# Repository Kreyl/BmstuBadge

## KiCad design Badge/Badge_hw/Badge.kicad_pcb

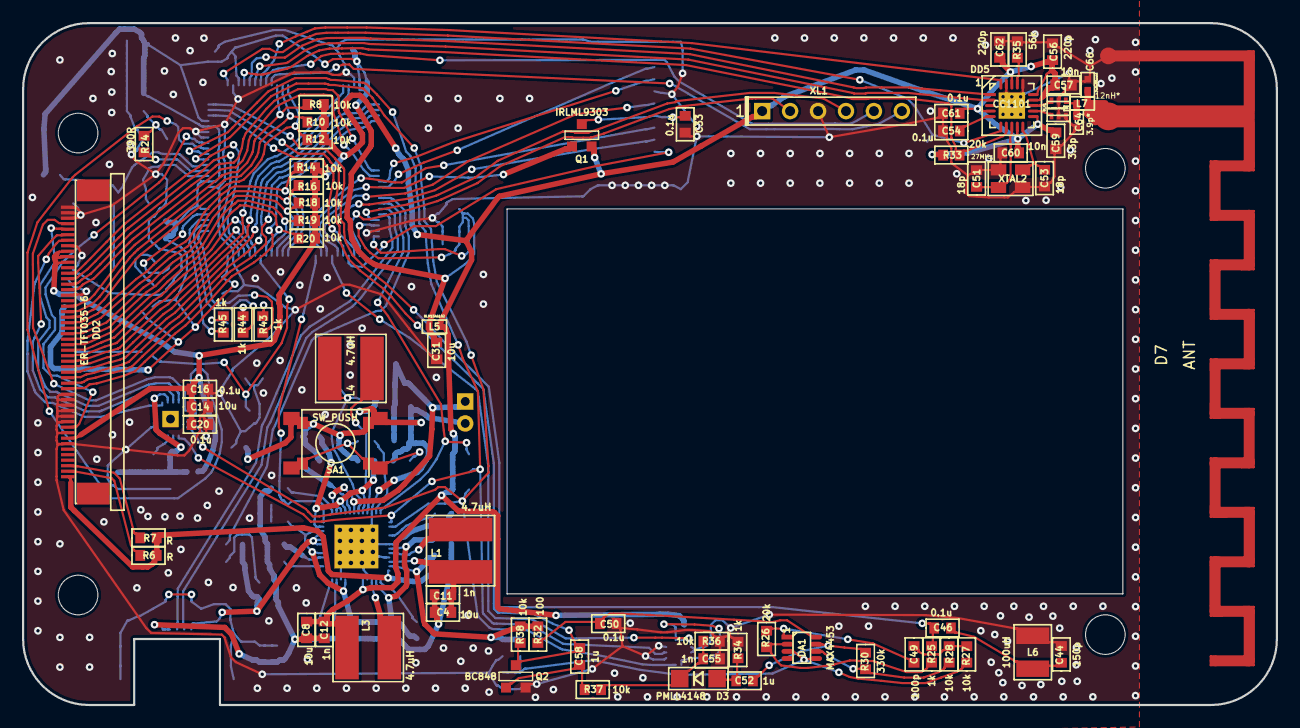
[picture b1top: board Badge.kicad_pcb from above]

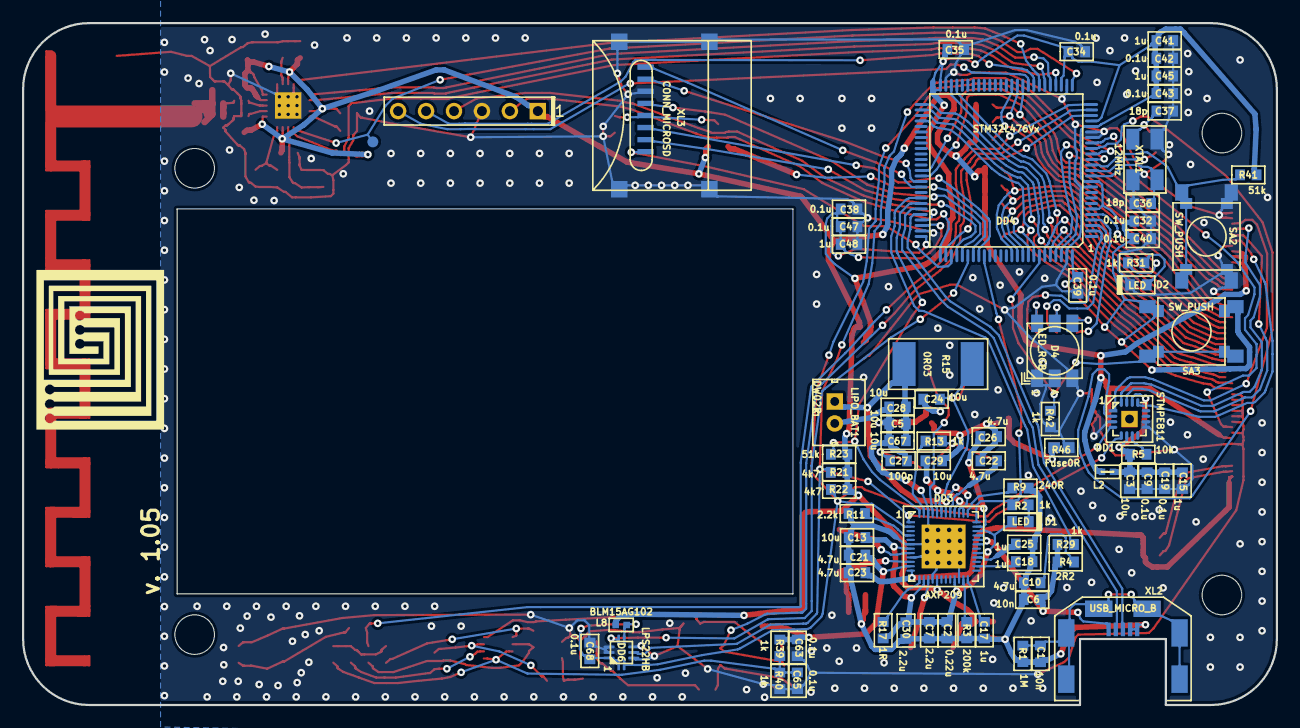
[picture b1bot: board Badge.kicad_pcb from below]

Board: 2 copper layers, 114.0 x 62.0 mm, 147 parts (77 on the bottom side), 118 nets.

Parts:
BLN1: BALUN868JOHANSON; BALUN_JOHANSON868
C1, C6, C57, C60: 10n; CAP_0603
C2: 0.22u; CAP_0603
C3, C4, C5, C8, C13, C14, C24, C28, C29, C31, C67: 10u; CAP_0603
C7, C30: 2.2u; CAP_0603
C9, C16, C19, C20, C32, C33, C34, C35, C38, C39, C40, C41, C43, C46, C47, C50, C54, C61, C63, C65, C68: 0.1u; CAP_0603
C10, C21, C22, C23, C26: 4.7u; CAP_0603
C11, C12, C55: 1n; CAP_0603
C15, C17, C18, C25, C42, C45, C48, C52, C58: 1u; CAP_0603
C27, C49: 100p; CAP_0603
C36, C37, C51, C53: 18p; CAP_0603
C44: 150p; CAP_0603
C56, C62: 220p; CAP_0603
C59: 3.3p; CAP_0603
C64: 3.9p*; CAP_0402
C66: DoNotMount; CAP_0402
D1, D2: LED; LED_0603
D3: PMLL4148; SOD80C
D4: LED_RGB; LED_5050
D7: ANT; ANTENNA_868_INV_F_SHARP
DA1: MAX4453; SOT23-8
DD1: STMPE811; QFN16_4x4_H
DD2: ER-TFT035-6; ER-CON50HT-1
DD3: AXP209; QFN48_EP_6x6_Pitch0.4mm
DD4: STM32L476Vx; LQFP100
DD5: CC1101; QFN20
DD6: LPS22HB; 10_2X2
L1, L3, L4: 4.7uH; IND_SDR0604
L2, L5, L8: BLM15AG102; IND_0402
L6: 100uH; IND_1812
L7: 12nH*; IND_0402
LIPO_BAT1: DW02R; WB-02(MW-2M)
Q1: IRLML9303; SOT23-3
Q2: BC848; SOT23-3
R1: 1M; RES_0603
R2, R13, R25, R29, R31, R34, R39, R40, R42, R43, R44, R45: 1k; RES_0603
R3: 200k; RES_0603
R4: 2R2; RES_0603
R5, R8, R10, R12, R14, R16, R18, R19, R20, R27, R28, R36, R37, R38: 10k; RES_0603
R6, R7: R; RES_0603
R9: 240R; RES_0603
R11: 2.2k; RES_0603
R15: 0R03; RES_2512
R17: 1R; RES_0603
R21, R22: 4k7; RES_0603
R23, R41: 51k; RES_0603
R24: 390R; RES_0603
R26, R33: 20k; RES_0603
R30: 330k; RES_0603
R32: 100; RES_0603
R35: 56k; RES_0603
R46: Fuse0R; RES_0603_FUSE
SA1, SA2, SA3: SW_PUSH; BTN_6x6_4x4
TP1: TESTPOINT; TESTPOINT_1MM
XL1: CONN_6; PLS-6
XL2: USB_MICRO_B; USBmicro_MOLEX_WM17142
XL3: CONN_MICROSD; MICROSD_CAP_FIX05A
XTAL1: 12MHz; 0503x4-4
XTAL2: 27MHz; 03225C4

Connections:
+2V5: C21.1, C63.1, DD3.11, R32.2, R38.2, R39.1
+3V3: C8.1, C12.1, C14.1, C16.1, C20.1, C56.1, C57.1, C59.1, C60.1, C61.1, C62.1, DD2.8, DD2.40, DD2.41, DD2.42, DD3.17, DD5.4, DD5.9, DD5.11, DD5.14, DD5.15, DD5.18, L2.2, L3.1, L5.2, L8.2, Q1.2, R8.2, R10.2, R12.2, R14.2, R16.2, R18.2, R19.2, R20.2, R21.2, R22.2, R23.2, R33.2, XL1.1
+3V3_120mA: C23.1, DD2.1, DD3.12, R6.2, R7.2
+5V: C6.1, DD3.31, DD3.32, DD3.33, R4.1, R29.1, XL2.1
+BATT: C5.1, C28.1, C67.1, DD3.38, DD3.39, DD3.42, LIPO_BAT1.1, R15.1
/ANT1: BLN1.1, C64.1, L7.2
/ANT2: C66.1, D7.~, L7.1
/CC_CS: DD4.29, DD5.7, R33.1
/CC_GDO0: DD4.26, DD5.6, TP1.1
/CC_MISO: DD4.31, DD5.2
/CC_MOSI: DD4.32, DD5.20
/CC_SCK: DD4.30, DD5.1
/CHARGING: DD3.36, DD4.84, R2.1
/DB0: DD2.32, DD4.35, R8.1
/DB1: DD2.31, DD4.36, R10.1
/DB2: DD2.30, DD4.37, R12.1
/DB3: DD2.29, DD4.89, R14.1
/DB4: DD2.28, DD4.90, R16.1
/DB5: DD2.27, DD4.91, R18.1
/DB6: DD2.26, DD4.92, R19.1
/DB7: DD2.25, DD4.93, R20.1
/DB8: DD2.24, DD4.95
/DB9: DD2.23, DD4.96
/DB10: DD2.22, DD4.47
/DB11: DD2.21, DD4.48
/DB12: DD2.20, DD4.51
/DB13: DD2.19, DD4.52
/DB14: DD2.18, DD4.53
/DB15: DD2.17, DD4.54
/DCDC_2: C4.1, C11.1, DD3.10, L1.1
/LCD_CS: DD2.38, DD4.97
/LCD_D/I_SLC: DD2.37, DD4.98
/LCD_RD: DD2.35, DD4.64
/LCD_RESET: DD2.10, DD4.18
/LCD_WR: DD2.36, DD4.63
/LCD_X+: DD1.13, DD2.44
/LCD_X-: DD1.16, DD2.46
/LCD_Y+: DD1.15, DD2.45
/LCD_Y-: DD1.1, DD2.47
/LDO_1: C25.1, DD3.28
/LDO_3: C22.1, DD3.41
/LX_2: DD3.8, L1.2
/LX_3: DD3.15, L3.2
/PRESSURE_INT: DD4.81, DD6.7
/PWR_IRQ: DD3.48, DD4.69, R23.1
/PWR_UNST: C2.1, C7.1, C13.1, C26.1, C29.2, C30.1, D1.A, DD3.7, DD3.14, DD3.21, DD3.29, DD3.34, DD3.35, DD3.40, DD3.44, R17.1
/RF1: BLN1.4, DD5.12
/RF2: BLN1.3, DD5.13
/SCL: DD1.4, DD3.2, DD4.15, DD6.2, R22.1
/SDA: DD1.5, DD3.1, DD4.16, DD6.4, R21.1
/SD_CLK: DD4.80, XL3.5
/SD_CMD: DD4.83, XL3.3
/SD_DAT0: DD4.65, XL3.7
/SD_DAT1: DD4.66, XL3.8
/SD_DAT2: DD4.78, XL3.1
/SD_DAT3: DD4.79, XL3.2
/SD_POWER: DD4.82, Q1.1
/SWD_CLK: DD4.76, XL1.2
/SWD_IO: DD4.72, XL1.4
/TOUCH_INT: DD1.2, DD4.17
/TOUCH_PWR: C3.1, C9.1, C15.1, C19.1, DD1.6, DD1.14, L2.1, R5.2
/UART_RX: DD4.34, XL1.6
/UART_TX: DD4.33, XL1.5
/USB_D+: DD4.71, XL2.3
/USB_D-: DD4.70, XL2.2
/klNFC_Modulation: DD4.23, DD4.77
/klNFC_Rx: C58.1, DD4.24, Q2.3, R38.1
/klNFC_Tx: C46.1, DD4.25, R25.2
GNDA: C1.2, C2.2, C4.2, C5.2, C6.2, C7.2, C8.2, C10.1, C11.2, C12.2, C13.2, C17.2, C18.2, C21.2, C22.2, C23.2, C24.2, C25.2, C26.2, C27.2, C28.2, C29.1, C30.2, C67.2, DD3.6, DD3.9, DD3.16, DD3.22, DD3.46, DD3.PAD, LIPO_BAT1.2, R1.2, R3.2, R9.1, R11.1, R46.1, SA1.2, XL2.4, XL2.5
GNDS: BLN1.2, BLN1.5, BLN1.6, C3.2, C9.2, C14.2, C15.2, C16.2, C19.2, C20.2, C31.2, C32.2, C33.2, C34.2, C35.2, C36.2, C37.2, C38.2, C39.2, C40.2, C41.2, C42.2, C43.2, C44.2, C45.2, C47.2, C48.2, C50.1, C51.2, C53.2, C54.2, C55.2, C56.2, C57.2, C59.2, C60.2, C61.2, C62.2, C63.2, C64.2, C65.2, C66.2, C68.2, D2.C, D4.1, D4.2, D4.3, D7.GND, DD1.3, DD1.9, DD1.10, DD2.7, DD2.9, DD2.11, DD2.12, DD2.13, DD2.14, DD2.15, DD2.16, DD2.34, DD2.43, DD2.48, DD2.49, DD2.50, DD4.10, DD4.19, DD4.20, DD4.27, DD4.49, DD4.74, DD4.99, DD5.16, DD5.19, DD5.PAD, DD6.3, DD6.5, DD6.8, DD6.9, L6.2, Q2.2, R34.1, R35.2, R36.1, R40.2, R42.1, R46.2, SA2.1, XL1.3, XL3.6, XL3.H, XTAL1.H, XTAL2.H
MCU_PWR: C31.1, C32.1, C34.1, C35.1, C38.1, C39.1, C40.1, C41.1, C42.1, C43.1, C45.1, C47.1, C48.1, DD4.6, DD4.11, DD4.21, DD4.22, DD4.28, DD4.50, DD4.73, DD4.75, DD4.100, L5.1, R41.2, SA3.2
unnamed: C1.1, R1.1, XL2.SHLD
unnamed: C10.2, R4.2
unnamed: C17.1, DD3.24
unnamed: C18.1, DD3.26
unnamed: C24.1, DD3.43, L4.1, R15.2
unnamed: C27.1, R13.1, SA1.1
unnamed: C33.1, Q1.3, XL3.4
unnamed: C36.1, DD4.12, XTAL1.1
unnamed: C37.1, R24.2, XTAL1.2
unnamed: C44.1, C46.2, L6.1
unnamed: C49.1, R27.2, R28.1
unnamed: C49.2, DA1.1, R26.1
unnamed: C50.2, DA1.8, R32.1
unnamed: C51.1, DD5.8, XTAL2.1
unnamed: C52.1, D3.A, R34.2
unnamed: C52.2, DA1.7, R30.1
unnamed: C53.1, DD5.10, XTAL2.2
unnamed: C54.1, DD5.5
unnamed: C55.1, D3.C, R36.2, R37.1
unnamed: C58.2, Q2.1, R37.2
unnamed: C68.1, DD6.1, DD6.6, DD6.10, L8.1
unnamed: D1.C, R2.2
unnamed: D2.A, R31.2
unnamed: D4.4, R45.1
unnamed: D4.5, R44.1
unnamed: D4.6, R43.1
unnamed: DA1.2, R25.1, R26.2
unnamed: DA1.6, R28.2, R30.2
unnamed: DD1.7, R5.1
unnamed: DD2.2, R6.1
unnamed: DD2.3, R7.1
unnamed: DD3.4, R11.2
unnamed: DD3.13, R17.2
unnamed: DD3.23, R3.1
unnamed: DD3.37, R9.2
unnamed: DD3.45, L4.2
unnamed: DD3.47, R13.2
unnamed: DD4.2, R43.2
unnamed: DD4.3, R44.2
unnamed: DD4.4, R45.2
unnamed: DD4.5, R31.1
unnamed: DD4.13, R24.1
unnamed: DD4.14, R41.1, SA2.2
unnamed: DD4.68, R29.2
unnamed: DD4.94, R42.2, SA3.1
unnamed: DD5.17, R35.1
VGND: C65.1, DA1.3, DA1.5, R27.1, R39.2, R40.1

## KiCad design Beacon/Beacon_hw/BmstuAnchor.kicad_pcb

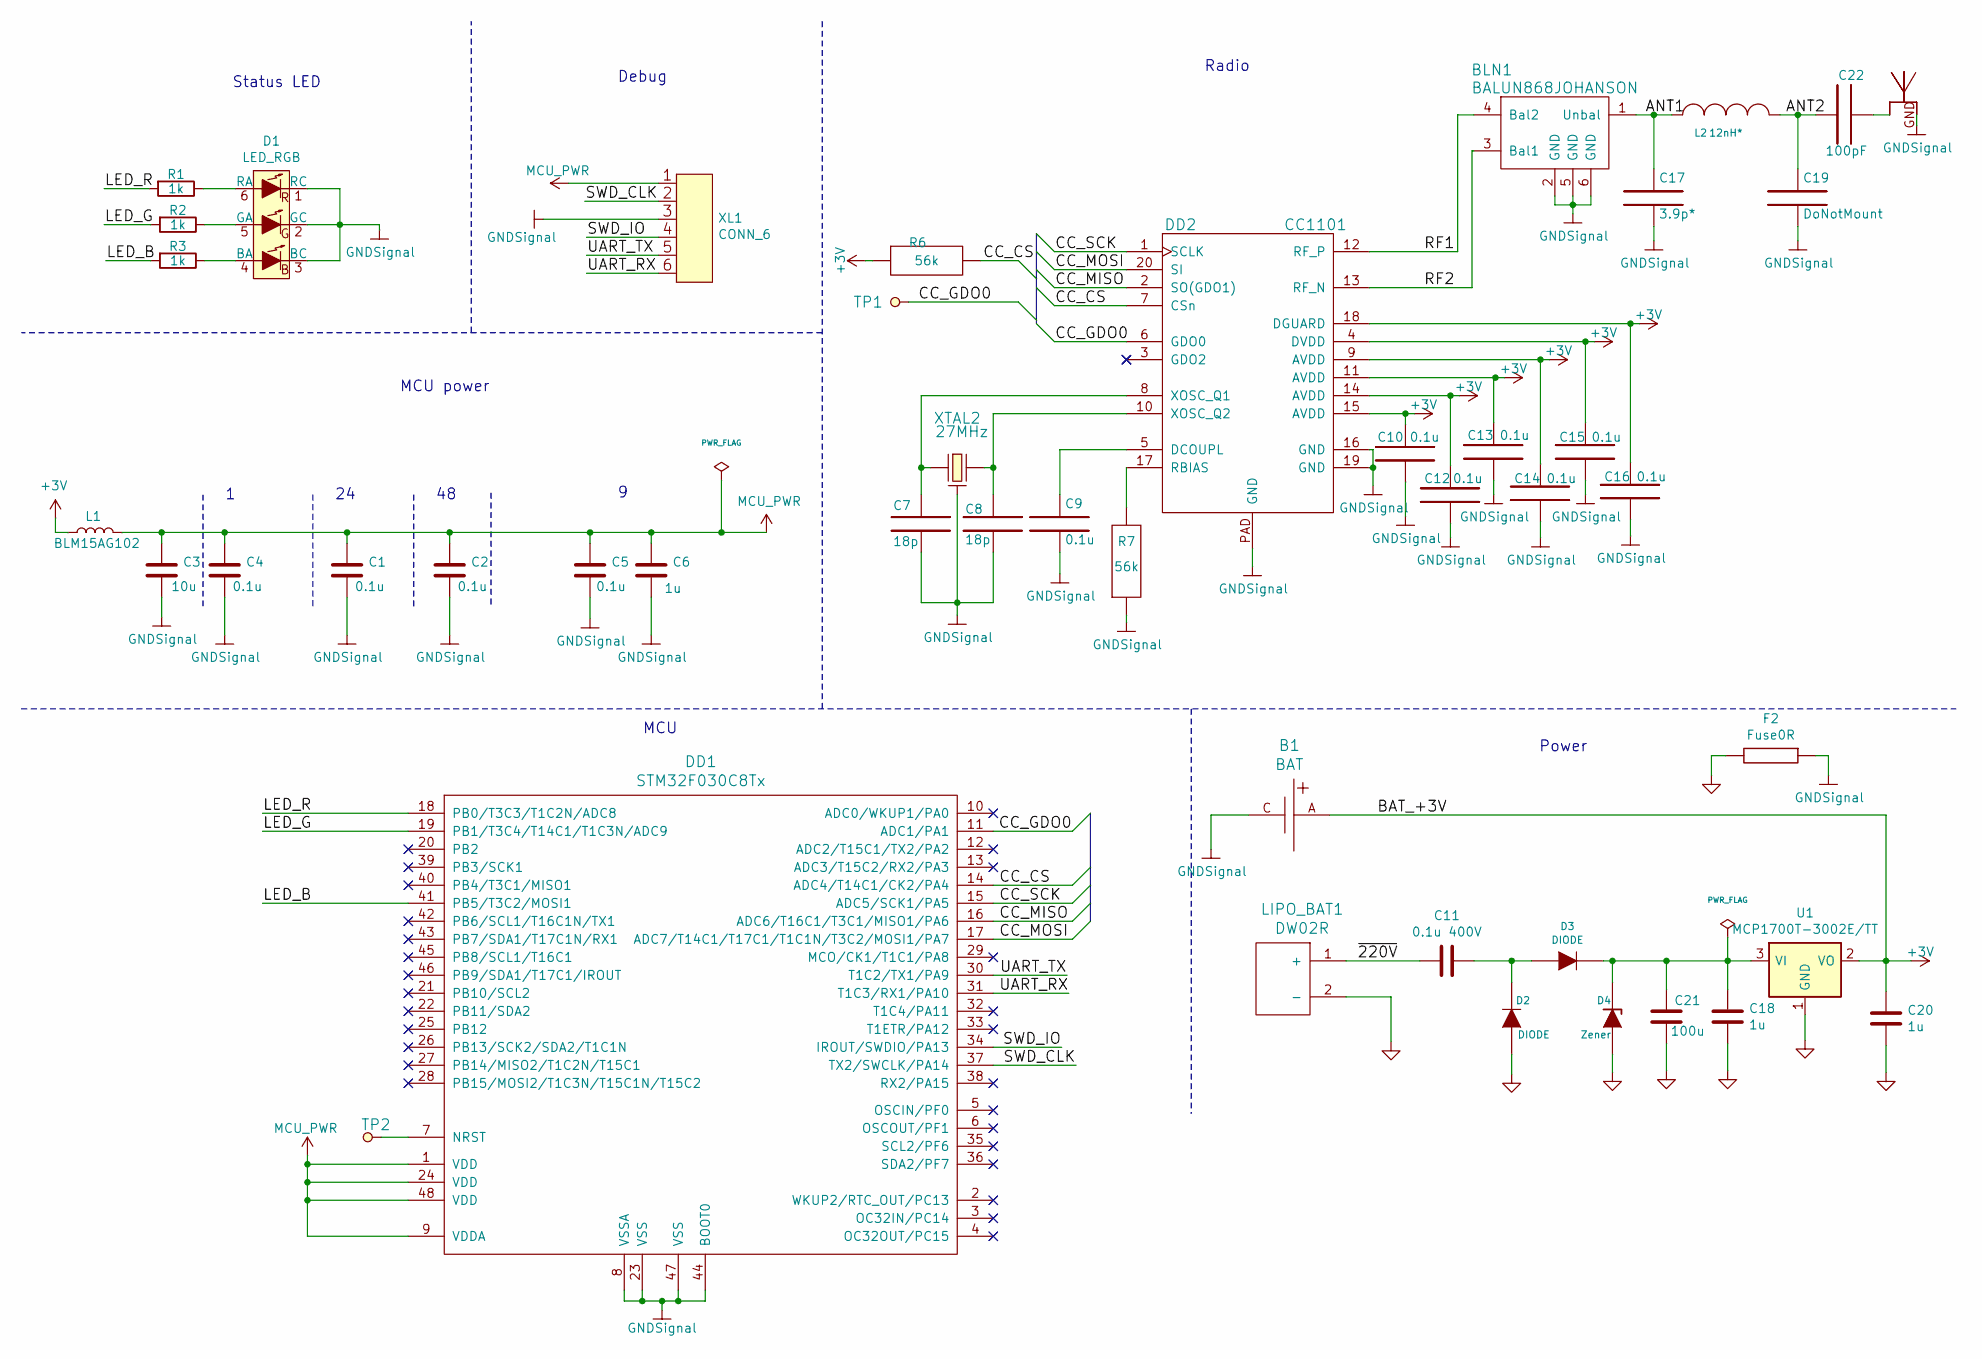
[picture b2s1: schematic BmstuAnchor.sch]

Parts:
B1: BAT; BATTERY_CH7410
BLN1: BALUN868JOHANSON; BALUN_JOHANSON868
C1, C2, C4, C5, C9, C10, C12, C13, C14, C15, C16: 0.1u; CAP_0603
C3: 10u; CAP_0603
C6, C18, C20: 1u; CAP_0603
C7, C8: 18p; CAP_0603
C11: 0.1u 400V; CAP_1812
C17: 3.9p*; CAP_0402
C19: DoNotMount; CAP_0402
C21: 100u; CAP_1210
C22: 100pF; CAP_0402
D1: LED_RGB; LED_5050
D2, D3: DIODE; SMA_DO214AC
D4: Zener; SOT23-3
D5: ANT; ANTENNA_868_INV_F_SHARP
DD1: STM32F030C8Tx; LQFP48
DD2: CC1101; QFN20
F2: Fuse0R; RES_0603_FUSE
L1: BLM15AG102; IND_0402
L2: 12nH*; IND_0402
LIPO_BAT1: DW02R; PLS-2-wide
R1, R2, R3: 1k; RES_0603
R6, R7: 56k; RES_0603
TP1, TP2: TESTPOINT; TESTPOINT_1MM
U1: MCP1700T-3002E/TT; SOT23-3
XL1: CONN_6; PLS-6
XTAL2: 27MHz; 03225C4

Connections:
+3V: B1.A, C10.1, C12.1, C13.1, C14.1, C15.1, C16.1, C20.1, DD2.4 (DVDD), DD2.9 (AVDD), DD2.11 (AVDD), DD2.14 (AVDD), DD2.15 (AVDD), DD2.18 (DGUARD), L1.1, R6.2, U1.2 (VO)
/ANT1: BLN1.1 (Unbal), C17.1, L2.2
/ANT2: C19.1, C22.2, L2.1
/CC_CS: DD1.14 (ADC4/T14C1/CK2/PA4), DD2.7 (CSn), R6.1
/CC_GDO0: DD1.11 (ADC1/PA1), DD2.6 (GDO0), TP1.1
/CC_MISO: DD1.16 (ADC6/T16C1/T3C1/MISO1/PA6), DD2.2 (SO(GDO1))
/CC_MOSI: DD1.17 (ADC7/T14C1/T17C1/T1C1N/T3C2/MOSI1/PA7), DD2.20 (SI)
/CC_SCK: DD1.15 (ADC5/SCK1/PA5), DD2.1 (SCLK)
/LED_B: DD1.41 (PB5/T3C2/MOSI1), R3.2
/LED_G: DD1.19 (PB1/T3C4/T14C1/T1C3N/ADC9), R2.2
/LED_R: DD1.18 (PB0/T3C3/T1C2N/ADC8), R1.2
/RF1: BLN1.4 (Bal2), DD2.12 (RF_P)
/RF2: BLN1.3 (Bal1), DD2.13 (RF_N)
/SWD_CLK: DD1.37 (TX2/SWCLK/PA14), XL1.2
/SWD_IO: DD1.34 (IROUT/SWDIO/PA13), XL1.4
/UART_RX: DD1.31 (T1C3/RX1/PA10), XL1.6
/UART_TX: DD1.30 (T1C2/TX1/PA9), XL1.5
/~220V: C11.2, LIPO_BAT1.1 (+)
GND: C18.2, C20.2, C21.2, D2.A, D4.1, F2.2, LIPO_BAT1.2 (-), U1.1 (GND)
GNDS: B1.C, BLN1.2 (GND), BLN1.5 (GND), BLN1.6 (GND), C1.2, C2.2, C3.2, C4.2, C5.2, C6.2, C7.2, C8.2, C9.2, C10.2, C12.2, C13.2, C14.2, C15.2, C16.2, C17.2, C19.2, D1.1 (RC), D1.2 (GC), D1.3 (BC), D5.GND, DD1.8 (VSSA), DD1.23 (VSS), DD1.44 (BOOT0), DD1.47 (VSS), DD2.16 (GND), DD2.19 (GND), DD2.PAD (GND), F2.1, R7.2, XL1.3, XTAL2.H
MCU_PWR: C1.1, C2.1, C3.1, C4.1, C5.1, C6.1, DD1.1 (VDD), DD1.9 (VDDA), DD1.24 (VDD), DD1.48 (VDD), L1.2, XL1.1
unnamed: C7.1, DD2.8 (XOSC_Q1), XTAL2.1
unnamed: C8.1, DD2.10 (XOSC_Q2), XTAL2.2
unnamed: C9.1, DD2.5 (DCOUPL)
unnamed: C11.1, D2.C, D3.A
unnamed: C18.1, C21.1, D3.C, D4.3, U1.3 (VI)
unnamed: C22.1, D5.~
unnamed: D1.4 (BA), R3.1
unnamed: D1.5 (GA), R2.1
unnamed: D1.6 (RA), R1.1
unnamed: DD1.7 (NRST), TP2.1
unnamed: DD2.17 (RBIAS), R7.1

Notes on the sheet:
Radio
Debug
Status LED
MCU power
MCU
Power

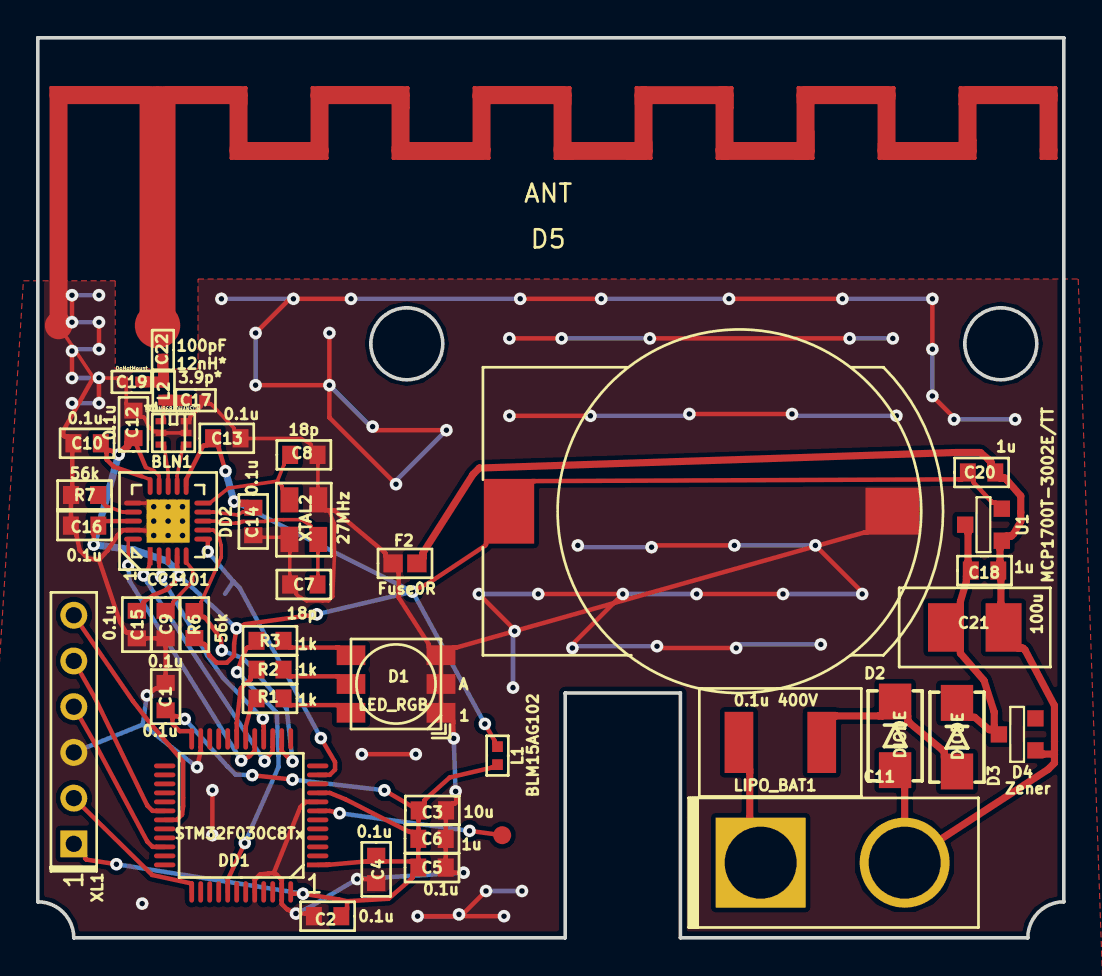
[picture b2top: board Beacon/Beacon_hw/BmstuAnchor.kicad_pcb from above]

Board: 2 copper layers, 57.0 x 50.0 mm, 45 parts (1 on the bottom side), 32 nets.

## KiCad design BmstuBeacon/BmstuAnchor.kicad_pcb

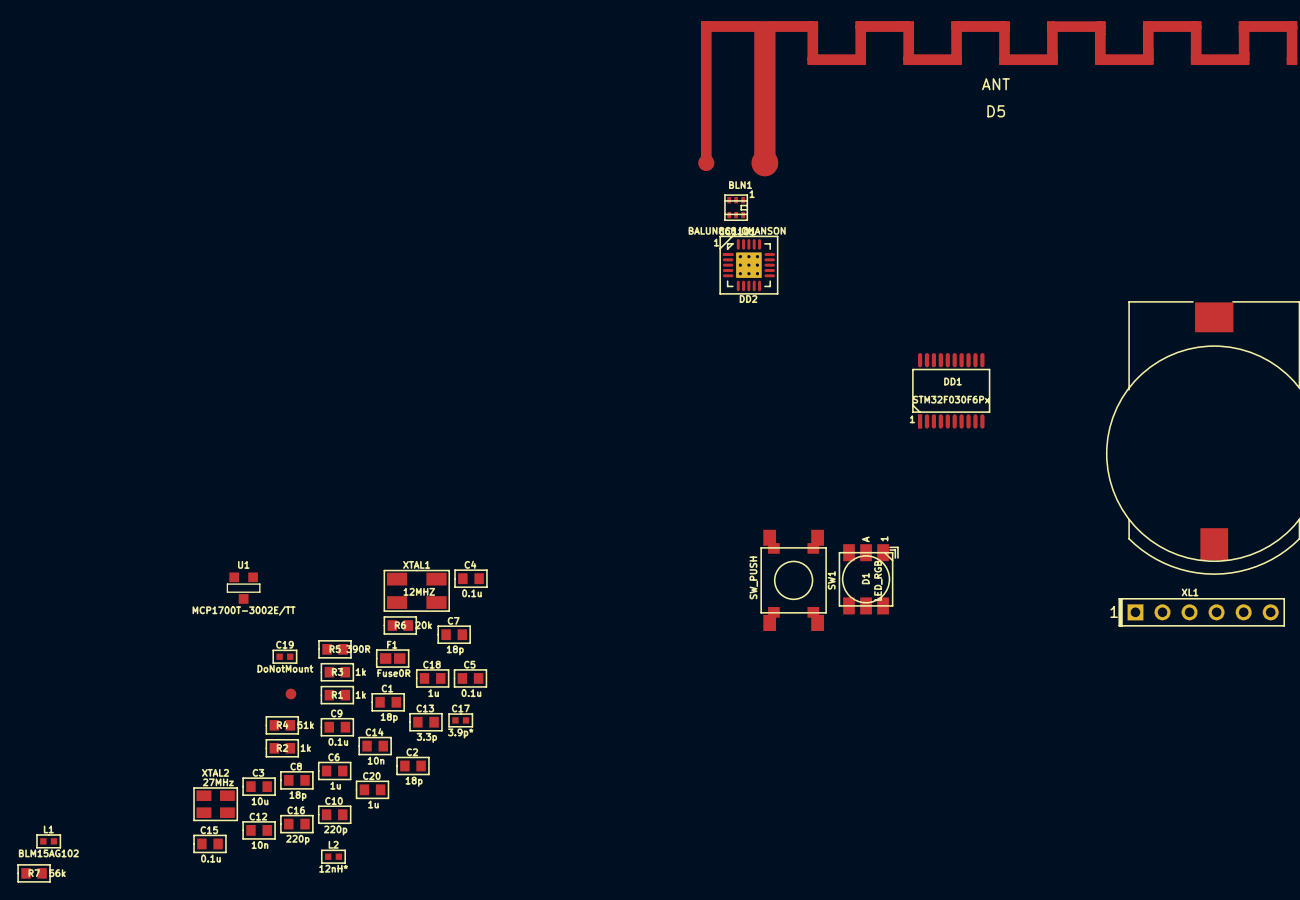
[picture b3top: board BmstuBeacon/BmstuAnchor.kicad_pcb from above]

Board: 2 copper layers, 41 parts (0 on the bottom side), 33 nets, no tracks yet.

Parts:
B1: BAT; BATTERY_CH7410
BLN1: BALUN868JOHANSON; BALUN_JOHANSON868
C1, C2, C7, C8: 18p; CAP_0603
C3: 10u; CAP_0603
C4, C5, C9, C15: 0.1u; CAP_0603
C6, C18, C20: 1u; CAP_0603
C10, C16: 220p; CAP_0603
C12, C14: 10n; CAP_0603
C13: 3.3p; CAP_0603
C17: 3.9p*; CAP_0402
C19: DoNotMount; CAP_0402
D1: LED_RGB; LED_5050
D5: ANT; ANTENNA_868_INV_F_SHARP
DD1: STM32F030F6Px; TSSOP20
DD2: CC1101; QFN20
F1: Fuse0R; RES_0603_FUSE
L1: BLM15AG102; IND_0402
L2: 12nH*; IND_0402
R1, R2, R3: 1k; RES_0603
R4: 51k; RES_0603
R5: 390R; RES_0603
R6: 20k; RES_0603
R7: 56k; RES_0603
SW1: SW_PUSH; BTN_6x6_4x4
TP1: TESTPOINT; TESTPOINT_1MM
U1: MCP1700T-3002E/TT; SOT23-3
XL1: CONN_6; PLS-6
XTAL1: 12MHZ; 0503x4-4
XTAL2: 27MHz; 03225C4

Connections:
+3V3: C10.1, C12.1, C13.1, C14.1, C15.1, C16.1, C20.1, DD2.4, DD2.9, DD2.11, DD2.14, DD2.15, DD2.18, L1.1, R6.2, U1.2, XL1.1
/ANT1: BLN1.1, C17.1, L2.2
/ANT2: C19.1, D5.~, L2.1
/BAT_+3V: B1.A, F1.2
/CC_CS: DD1.10, DD2.7, R6.1
/CC_GDO0: DD1.17, DD2.6, TP1.1
/CC_MISO: DD1.12, DD2.2
/CC_MOSI: DD1.13, DD2.20
/CC_SCK: DD1.11, DD2.1
/LED_B: DD1.18, R3.2
/LED_G: DD1.7, R2.2
/LED_R: DD1.6, R1.2
/RF1: BLN1.4, DD2.12
/RF2: BLN1.3, DD2.13
/SWD_CLK: DD1.20, XL1.2
/SWD_IO: DD1.19, XL1.4
/UART_RX: DD1.9, XL1.6
/UART_TX: DD1.8, XL1.5
GNDA: B1.C, C18.2, C20.2, U1.1
GNDS: BLN1.2, BLN1.5, BLN1.6, C1.2, C2.2, C3.2, C4.2, C5.2, C6.2, C7.2, C8.2, C9.2, C10.2, C12.2, C13.2, C14.2, C15.2, C16.2, C17.2, C19.2, D1.1, D1.2, D1.3, D5.GND, DD1.1, DD1.15, DD2.16, DD2.19, DD2.PAD, R7.2, SW1.1, XL1.3, XTAL1.H, XTAL2.H
MCU_PWR: C3.1, C4.1, C5.1, C6.1, DD1.5, DD1.16, L1.2, R4.2
unnamed: C1.1, DD1.2, XTAL1.1
unnamed: C2.1, R5.2, XTAL1.2
unnamed: C7.1, DD2.8, XTAL2.1
unnamed: C8.1, DD2.10, XTAL2.2
unnamed: C9.1, DD2.5
unnamed: C18.1, F1.1, U1.3
unnamed: D1.4, R3.1
unnamed: D1.5, R2.1
unnamed: D1.6, R1.1
unnamed: DD1.3, R5.1
unnamed: DD1.4, R4.1, SW1.2
unnamed: DD2.17, R7.1

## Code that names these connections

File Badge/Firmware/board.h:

/*
 * board.h
 *
 *  Created on: 12 ñåíò. 2015 ã.
 *      Author: Kreyl
 */

#pragma once

#include <inttypes.h>

// ==== General ====
#define BOARD_NAME          "BmstuBadge"
#define APP_NAME            "Badge01"

// MCU type as defined in the ST header.
#define STM32L476xx

// Freq of external crystal if any. Leave it here even if not used.
#define CRYSTAL_FREQ_HZ         12000000

// OS timer settings
#define STM32_ST_IRQ_PRIORITY   2
#define STM32_ST_USE_TIMER      5
#define SYS_TIM_CLK             (Clk.APB1FreqHz)    // Timer 5 is clocked by APB1

//  Periphery
#define I2C1_ENABLED            FALSE
#define I2C2_ENABLED            FALSE
#define I2C3_ENABLED            TRUE
#define SIMPLESENSORS_ENABLED   FALSE
#define BUTTONS_ENABLED         FALSE

#define ADC_REQUIRED            FALSE
#define STM32_DMA_REQUIRED      TRUE    // Leave this macro name for OS

#if 1 // ========================== GPIO =======================================
// EXTI
#define INDIVIDUAL_EXTI_IRQ_REQUIRED    FALSE

// Buttons
#define BTN_COM_PIN     GPIOA, 0, pudPullUp
#define BTN_UP_PIN      GPIOA, 1, pudPullUp
#define BTN_DOWN_PIN    GPIOC, 0, pudPullUp

// UART
#define UART_GPIO       GPIOC
#define UART_TX_PIN     4
#define UART_RX_PIN     5
#define UART_AF         AF7 // for all USARTs

// RGB LED
#define LED_GREEN_CH    { GPIOE, 3, TIM3, 1, invNotInverted, omPushPull, 255 }
#define LED_RED_CH      { GPIOE, 4, TIM3, 2, invNotInverted, omPushPull, 255 }
#define LED_BLUE_CH     { GPIOE, 5, TIM3, 3, invNotInverted, omPushPull, 255 }

// I2C
#define I2C1_GPIO       GPIOB
#define I2C1_SCL        6
#define I2C1_SDA        7
#define I2C2_GPIO       GPIOB
#define I2C2_SCL        10
#define I2C2_SDA        11
#define I2C3_GPIO       GPIOC
#define I2C3_SCL        0
#define I2C3_SDA        1
// I2C Alternate Function
#define I2C_AF          AF4

// SD
#define SD_PWR_PIN      GPIOD, 1
#define SD_AF           AF12
#define SD_DAT0         GPIOC,  8, omPushPull, pudPullUp, SD_AF
#define SD_DAT1         GPIOC,  9, omPushPull, pudPullUp, SD_AF
#define SD_DAT2         GPIOC, 10, omPushPull, pudPullUp, SD_AF
#define SD_DAT3         GPIOC, 11, omPushPull, pudPullUp, SD_AF
#define SD_CLK          GPIOC, 12, omPushPull, pudNone,   SD_AF
#define SD_CMD          GPIOD,  2, omPushPull, pudPullUp, SD_AF


//LCD
#define LCD_DATA_GPIO   GPIOB
#define LCD_RESET       GPIOC, 3
#define LCD_CS          GPIOE, 0
#define LCD_DC          GPIOE, 1
#define LCD_WR          GPIOC, 6
#define LCD_RD          GPIOC, 7

// Touch
#define TOUCH_INT_GPIO  GPIOC
#define TOUCH_INT_PIN   2


#endif // GPIO

//#if 1 // =========================== SPI =======================================
//#define CC_SPI          SPI1
//#define CC_SPI_AF       AF5
//
//#endif

#if 1 // ========================== USART ======================================
#define PRINTF_FLOAT_EN FALSE
#define CMD_UART        USART3
#define UART_USE_INDEPENDENT_CLK    TRUE
#define UART_TXBUF_SZ   1024
#endif

#if 1 // =========================== I2C =======================================
// i2cclkPCLK1, i2cclkSYSCLK, i2cclkHSI
#define I2C_CLK_SRC     i2cclkHSI
#define I2C_BAUDRATE_HZ 400000
#endif

#if ADC_REQUIRED // ======================= Inner ADC ==========================
// Clock divider: clock is generated from the APB2
#define ADC_CLK_DIVIDER		adcDiv2

// ADC channels
#define ADC_BATTERY_CHNL 	14
// ADC_VREFINT_CHNL
#define ADC_CHANNELS        { ADC_BATTERY_CHNL, ADC_VREFINT_CHNL }
#define ADC_CHANNEL_CNT     2   // Do not use countof(AdcChannels) as preprocessor does not know what is countof => cannot check
#define ADC_SAMPLE_TIME     ast24d5Cycles
#define ADC_OVERSAMPLING_RATIO  64   // 1 (no oversampling), 2, 4, 8, 16, 32, 64, 128, 256
#endif

#if 1 // =========================== DMA =======================================
// ==== Uart ====
// Remap is made automatically if required
#define UART_DMA_TX     STM32_DMA1_STREAM2
#define UART_DMA_RX     STM32_DMA1_STREAM3
#define UART_DMA_CHNL   2

// ==== I2C ====
#define I2C1_DMA_TX     STM32_DMA1_STREAM6
#define I2C1_DMA_RX     STM32_DMA1_STREAM7
#define I2C1_DMA_CHNL   3
#define I2C2_DMA_TX     STM32_DMA1_STREAM4
#define I2C2_DMA_RX     STM32_DMA1_STREAM5
#define I2C2_DMA_CHNL   3
#define I2C3_DMA_TX     STM32_DMA1_STREAM2
#define I2C3_DMA_RX     STM32_DMA1_STREAM3
#define I2C3_DMA_CHNL   3

// ==== SDMMC ====
#define STM32_SDC_SDMMC1_DMA_STREAM   STM32_DMA_STREAM_ID(2, 5)

#if ADC_REQUIRED
#define ADC_DMA         STM32_DMA1_STREAM1
#define ADC_DMA_MODE    STM32_DMA_CR_CHSEL(0) |   /* DMA1 Stream1 Channel0 */ \
                        DMA_PRIORITY_LOW | \
                        STM32_DMA_CR_MSIZE_HWORD | \
                        STM32_DMA_CR_PSIZE_HWORD | \
                        STM32_DMA_CR_MINC |       /* Memory pointer increase */ \
                        STM32_DMA_CR_DIR_P2M |    /* Direction is peripheral to memory */ \
                        STM32_DMA_CR_TCIE         /* Enable Transmission Complete IRQ */
#endif // ADC

#endif // DMA

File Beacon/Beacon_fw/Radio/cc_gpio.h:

/*
 * cc_gpio.h
 *
 *  Created on: 22 ìàðòà 2018 ã.
 *      Author: home
 */

#pragma once

//Pins
#define CC_GPIO		GPIOA
#define CC_GDO0		1
#define CC_CS		4
#define CC_SCK		5
#define CC_MISO		6
#define CC_MOSI		7


//SPI
#define CC_SPI		SPI1
#if defined STM32L1XX
#define CC_SPI_AF	AF5
#elif defined STM32F030
#define CC_SPI_AF	AF0
#endif

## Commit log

2016-09-27 + CubeMX project
2016-10-15 + KiCAD project + AXP209 as KiCAD component
2016-10-17 + Power Supply in process (OLinuXino redrawing)
2016-10-19 + library with display component inside
2016-10-19 * added display component & interface
2016-10-20 + Touch Interface
2016-10-23 + radio
2016-10-24 AXP209_full_power_supply_circuit
2016-10-24 * merge
2016-10-24 * power supply circuit modified
2016-11-04 +klNFC & uSD card
2016-11-04 04/11 commit (* power modified)
2016-11-06 *GND circuit, Power Supply modified
2016-11-13 + SolidWorks drawings
2016-11-18 * ground updated
2016-11-19 *GOST redraw
2016-12-09 update 9.12 - scheme + case updated
2017-02-09 9.2 +pcb
2017-02-09 +antenna
2017-02-15 * pcb redraw + barometer scheme
2017-02-20 * schematic, footprints
2017-02-22 +pcb
2017-02-27 pcb full 1.0
2017-03-07 *pcb 2.0
2017-08-06 Working FW project
2017-08-13 *case updated
2017-08-13 merge
2017-08-27 +BmstuBeacon_hw
2017-08-27 *structured
2017-09-03 +beacon pcb
2017-10-19 beacon pcb redraw badge fw upd
2017-11-06 *pcb upd, C before antenna added
2017-11-06 AXP209 works
2017-11-12 +axp library *beaco pcb upd
2017-11-21 +beacon: gerber, fw upd
2017-11-21 AXP LDO fixed
2017-11-21 + LCD first step
2017-11-29 + bmp lib , *ili: bmp image show func, + sd card: bmp read
2017-11-30 image load time optimization + little touch changes
2018-01-23 display lib upd
2018-03-06 +сс1101 fw start +beacon fw
2018-05-05 Navigation first commit
2018-05-25 badge
